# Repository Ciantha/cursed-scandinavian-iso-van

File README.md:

# cursed-scandinavian-iso-van
CC BY-NC 4.0

PCB work finished by the very kind josh-l-wang

## Images

## Disclaimer
The PCB design has been tested and confirmed to work. 
However, no one associated with this project (or anyone else) is liable if you end up with a non-functional pcb. 
Order at your own risk. Support will not be provided.

## Footprints and other tools

Uses footprints from https://github.com/ebastler/marbastlib
Thanks to zykrah for the very convenient KLE plugin https://github.com/zykrah/kicad-kle-placer#installation-kicad-7

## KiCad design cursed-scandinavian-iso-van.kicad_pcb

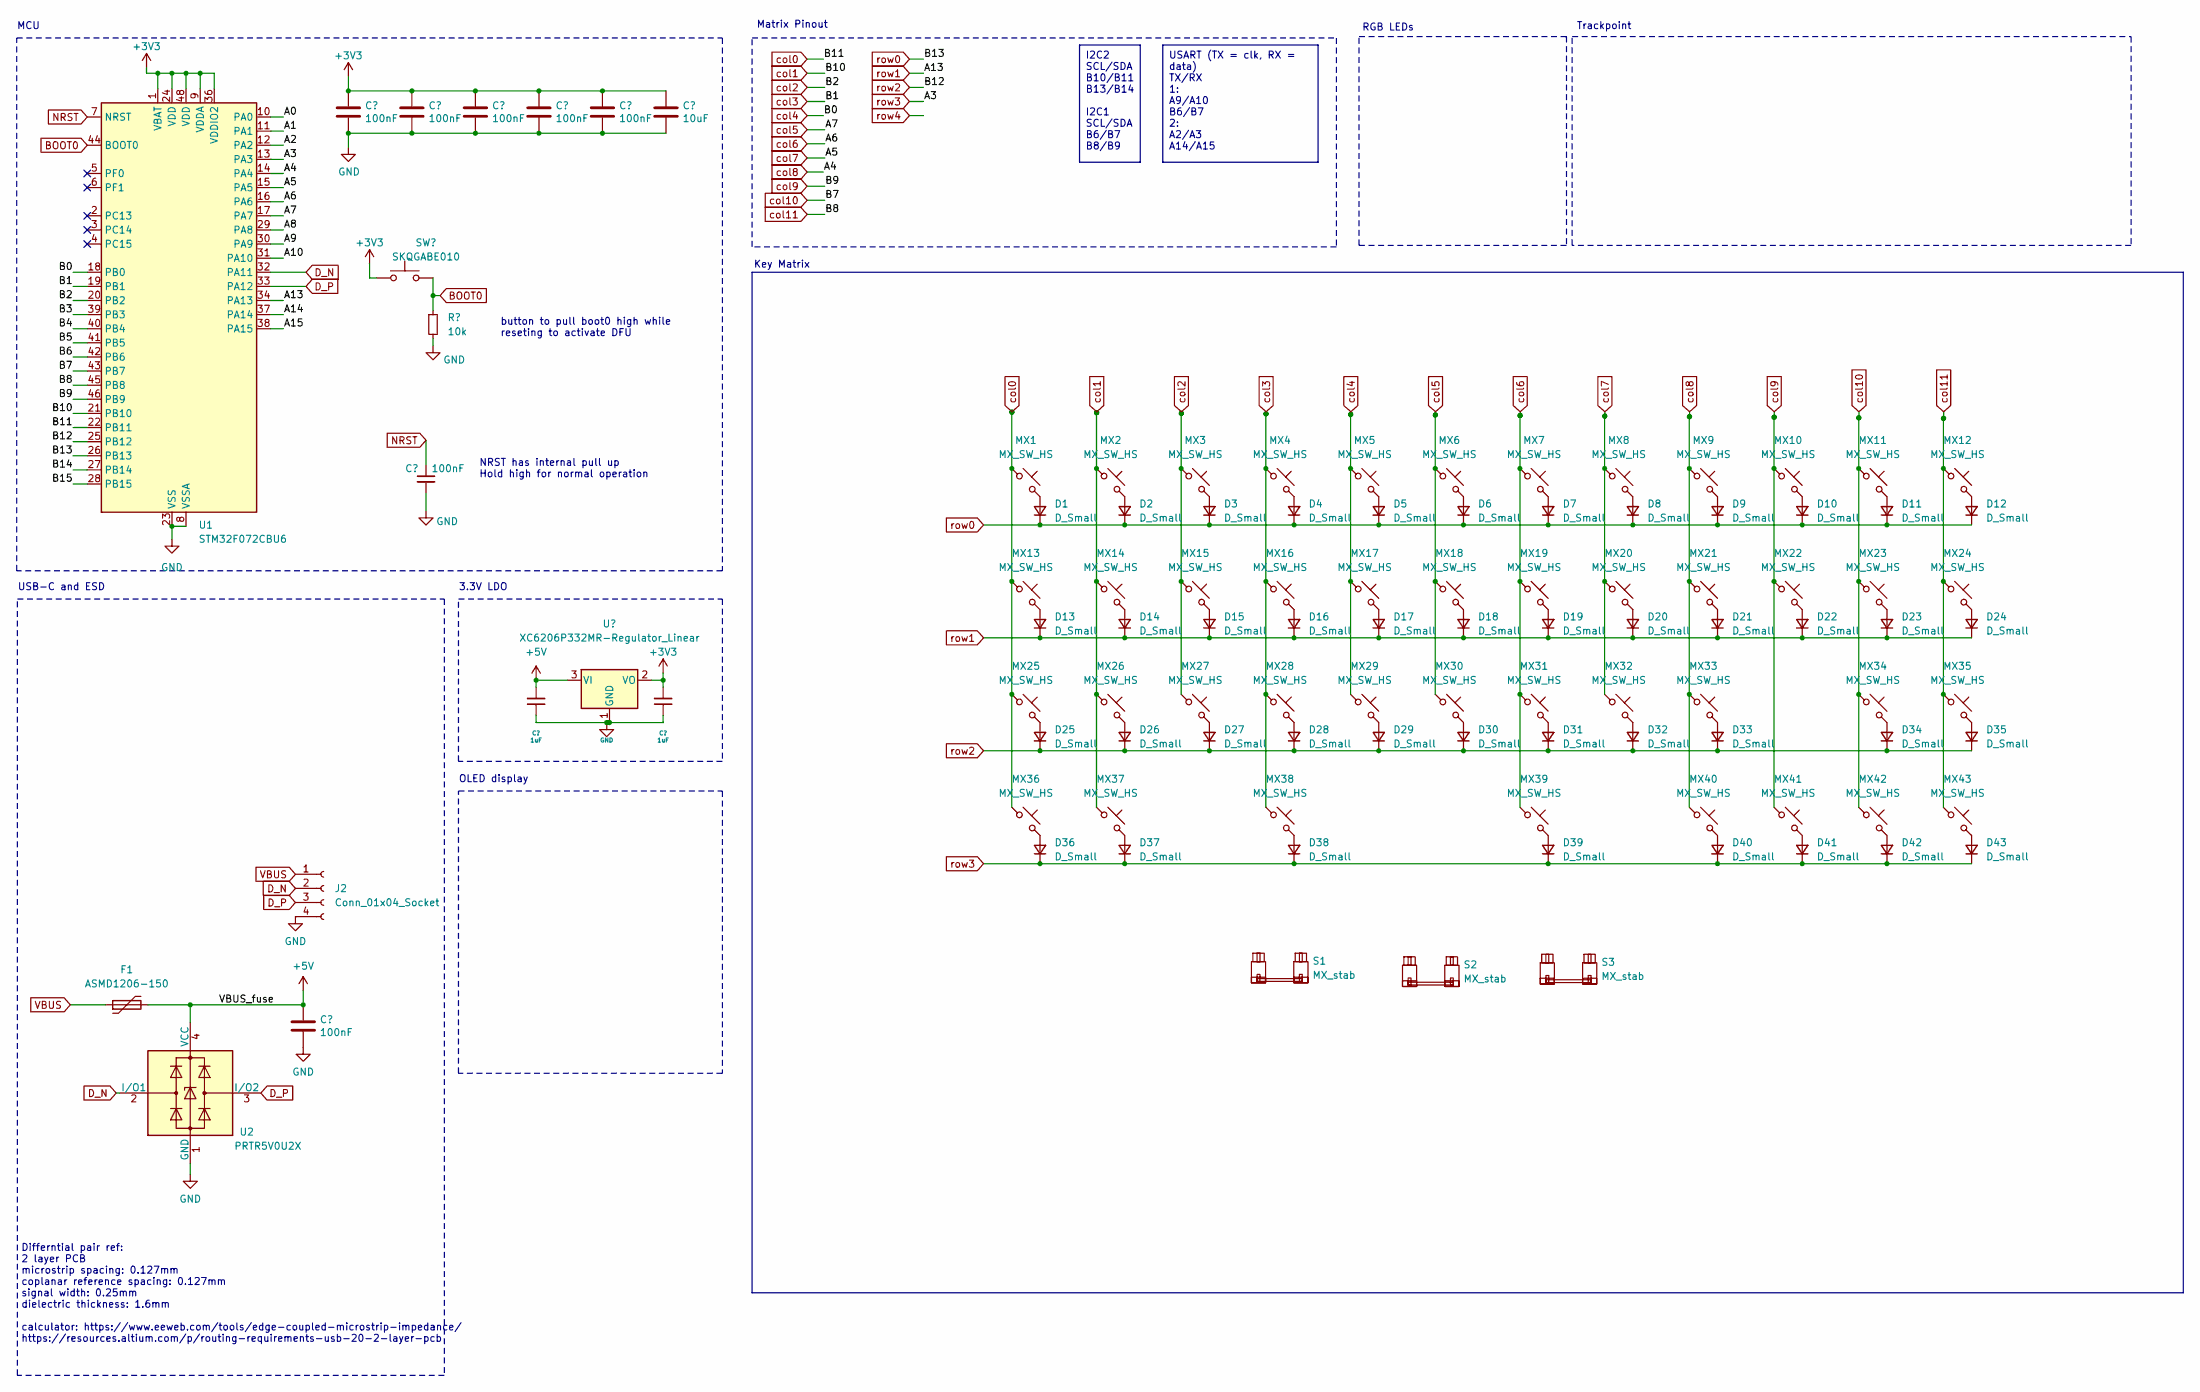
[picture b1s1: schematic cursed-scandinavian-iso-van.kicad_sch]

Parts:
C1, C2, C3, C4, C5, C7, C10: 100nF; C_0402_1005Metric; LCSC C307331
C6: 10uF; C_0603_1608Metric; LCSC C96446
C8, C9: 1uF; C_0402_1005Metric; LCSC C52923
D1, D2, D3, D4, D5, D6, D7, D8, D9, D10, D11, D12, D13, D14, D15, D16, D17, D18, D19, D20, D21, D22, D23, D24, D25, D26, D27, D28, D29, D30, D31, D32, D33, D34, D35, D36, D37, D38, D39, D40, D41, D42, D43: D_Small; D_SOD-123
F1: ASMD1206-150; Fuse_1206_3216Metric; LCSC C135341
J2: Conn_01x04_Socket; JST_SH_SM04B-SRSS-TB_1x04-1MP_P1.00mm_Horizontal
MX1, MX2, MX3, MX4, MX5, MX6, MX7, MX8, MX9, MX11, MX12, MX14, MX15, MX16, MX17, MX18, MX19, MX20, MX21, MX22, MX23, MX24, MX26, MX27, MX28, MX29, MX30, MX31, MX32, MX33, MX34, MX35, MX36, MX38, MX39, MX41, MX42, MX43: MX_SW_HS; SW_MX_HS_1u
MX10: MX_SW_HS; SW_MX_HS_1.75u
MX13, MX37, MX40: MX_SW_HS; SW_MX_HS_1.25u
MX25: MX_SW_HS; SW_MX_HS_1.5u
R1: 10k; R_0402_1005Metric; LCSC C25905
S1: MX_stab; STAB_MX_P_3u
S2: MX_stab; STAB_MX_P_2.75u
S3: MX_stab; STAB_MX_P_ISO-ROT
SW1: SKQGABE010; SW_SPST_SKQG_WithoutStem; LCSC C318884
U1: STM32F072CBU6; LQFP-48-1EP_7x7mm_P0.5mm_EP3.6x3.6mm; JlcRotOffset 90
U2: PRTR5V0U2X; SOT-143; LCSC C2827688
U3: XC6206P332MR-Regulator_Linear; SOT-23; LCSC C5446

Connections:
+3V3: C1.1, C2.1, C3.1, C4.1, C5.1, C6.1, C9.2, SW1.1, U1.1 (VBAT), U1.9 (VDDA), U1.24 (VDD), U1.36 (VDDIO2), U1.48 (VDD), U3.2 (VO)
+5V: C8.2, C10.1, F1.2, U2.4 (VCC), U3.3 (VI)
/A0: U1.10 (PA0)
/A1: U1.11 (PA1)
/A2: U1.12 (PA2)
/A8: U1.29 (PA8)
/A9: U1.30 (PA9)
/A10: U1.31 (PA10)
/A14: U1.37 (PA14)
/A15: U1.38 (PA15)
/B3: U1.39 (PB3)
/B4: U1.40 (PB4)
/B5: U1.41 (PB5)
/B6: U1.42 (PB6)
/B14: U1.27 (PB14)
/B15: U1.28 (PB15)
BOOT0: R1.1, SW1.2, U1.44 (BOOT0)
D_N: J2.2, U1.32 (PA11), U2.2 (I/O1)
D_P: J2.3, U1.33 (PA12), U2.3 (I/O2)
GND: C1.2, C2.2, C3.2, C4.2, C5.2, C6.2, C7.2, C8.1, C9.1, C10.2, J2.4, R1.2, U1.8 (VSSA), U1.23 (VSS), U1.35 (VSS), U1.47 (VSS), U1.49 (VSS), U2.1 (GND), U3.1 (GND)
NRST: C7.1, U1.7 (NRST)
unnamed: D1.2 (A), MX1.2
unnamed: D2.2 (A), MX2.2
unnamed: D3.2 (A), MX3.2
unnamed: D4.2 (A), MX4.2
unnamed: D5.2 (A), MX5.2
unnamed: D6.2 (A), MX6.2
unnamed: D7.2 (A), MX7.2
unnamed: D8.2 (A), MX8.2
unnamed: D9.2 (A), MX9.2
unnamed: D10.2 (A), MX10.2
unnamed: D11.2 (A), MX11.2
unnamed: D12.2 (A), MX12.2
unnamed: D13.2 (A), MX13.2
unnamed: D14.2 (A), MX14.2
unnamed: D15.2 (A), MX15.2
unnamed: D16.2 (A), MX16.2
unnamed: D17.2 (A), MX17.2
unnamed: D18.2 (A), MX18.2
unnamed: D19.2 (A), MX19.2
unnamed: D20.2 (A), MX20.2
unnamed: D21.2 (A), MX21.2
unnamed: D22.2 (A), MX22.2
unnamed: D23.2 (A), MX23.2
unnamed: D24.2 (A), MX24.2
unnamed: D25.2 (A), MX25.2
unnamed: D26.2 (A), MX26.2
unnamed: D27.2 (A), MX27.2
unnamed: D28.2 (A), MX28.2
unnamed: D29.2 (A), MX29.2
unnamed: D30.2 (A), MX30.2
unnamed: D31.2 (A), MX31.2
unnamed: D32.2 (A), MX32.2
unnamed 53: D33.2 (A), MX33.2; also elsewhere on the board
unnamed: D34.2 (A), MX34.2
unnamed: D35.2 (A), MX35.2
unnamed: D36.2 (A), MX36.2
unnamed: D37.2 (A), MX37.2
unnamed: D38.2 (A), MX38.2
unnamed: D39.2 (A), MX39.2
unnamed: D40.2 (A), MX40.2
unnamed: D41.2 (A), MX41.2
unnamed: D42.2 (A), MX42.2
unnamed: D43.2 (A), MX43.2
VBUS: F1.1, J2.1
col0: MX1.1, MX13.1, MX25.1, MX36.1, U1.22 (PB11)
col1: MX2.1, MX14.1, MX26.1, MX37.1, U1.21 (PB10)
col2: MX3.1, MX15.1, MX27.1, U1.20 (PB2)
col3: MX4.1, MX16.1, MX28.1, MX38.1, U1.19 (PB1)
col4: MX5.1, MX17.1, MX29.1, U1.18 (PB0)
col5: MX6.1, MX18.1, MX30.1, U1.17 (PA7)
col6: MX7.1, MX19.1, MX31.1, MX39.1, U1.16 (PA6)
col7: MX8.1, MX20.1, MX32.1, U1.15 (PA5)
col8: MX9.1, MX21.1, MX33.1, MX40.1, U1.14 (PA4); also elsewhere on the board
col9: MX10.1, MX22.1, MX41.1, U1.46 (PB9)
col10: MX11.1, MX23.1, MX34.1, MX42.1, U1.43 (PB7)
col11: MX12.1, MX24.1, MX35.1, MX43.1, U1.45 (PB8)
row0: D1.1 (K), D2.1 (K), D3.1 (K), D4.1 (K), D5.1 (K), D6.1 (K), D7.1 (K), D8.1 (K), D9.1 (K), D10.1 (K), D11.1 (K), D12.1 (K), U1.26 (PB13)
row1: D13.1 (K), D14.1 (K), D15.1 (K), D16.1 (K), D17.1 (K), D18.1 (K), D19.1 (K), D20.1 (K), D21.1 (K), D22.1 (K), D23.1 (K), D24.1 (K), U1.34 (PA13)
row2: D25.1 (K), D26.1 (K), D27.1 (K), D28.1 (K), D29.1 (K), D30.1 (K), D31.1 (K), D32.1 (K), D33.1 (K), D34.1 (K), D35.1 (K), U1.25 (PB12)
row3: D36.1 (K), D37.1 (K), D38.1 (K), D39.1 (K), D40.1 (K), D41.1 (K), D42.1 (K), D43.1 (K), U1.13 (PA3)

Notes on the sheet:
USART (TX = clk, RX = data) TX/RX 1: A9/A10 B6/B7 2: A2/A3 A14/A15
I2C2 SCL/SDA B10/B11 B13/B14 I2C1 SCL/SDA B6/B7 B8/B9
button to pull boot0 high while reseting to activate DFU
Matrix Pinout
MCU
RGB LEDs
Trackpoint
3.3V LDO
USB-C and ESD
OLED display
NRST has internal pull up Hold high for normal operation
Differntial pair ref: 2 layer PCB microstrip spacing: 0.127mm coplanar reference spacing: 0.127mm signal width: 0.25mm dielectric thickness: 1.6mm calculator: https://www.eeweb.com/tools/edge-coupled-microstrip-impedance/ https://resources.altium.com/p/routing-requirements-usb-20-2-layer-pcb
Key Matrix

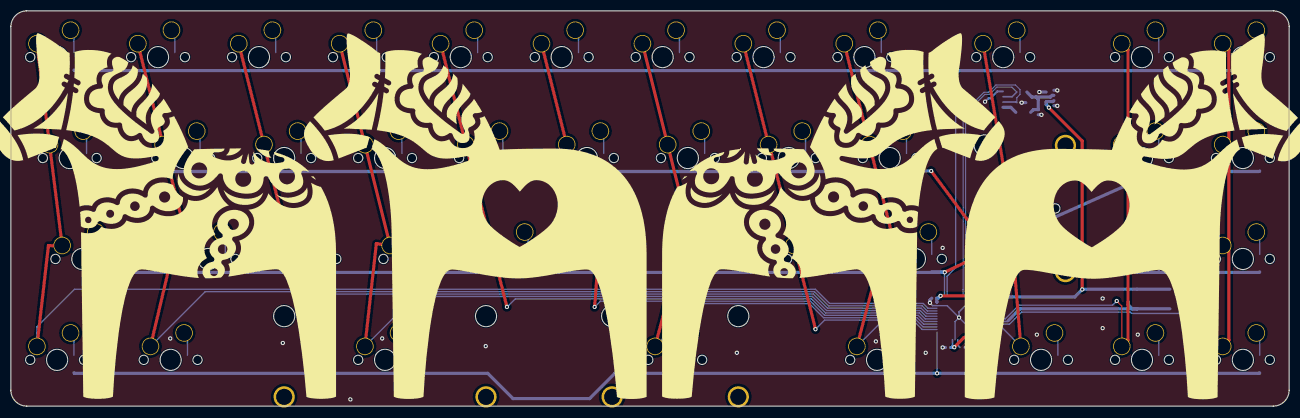
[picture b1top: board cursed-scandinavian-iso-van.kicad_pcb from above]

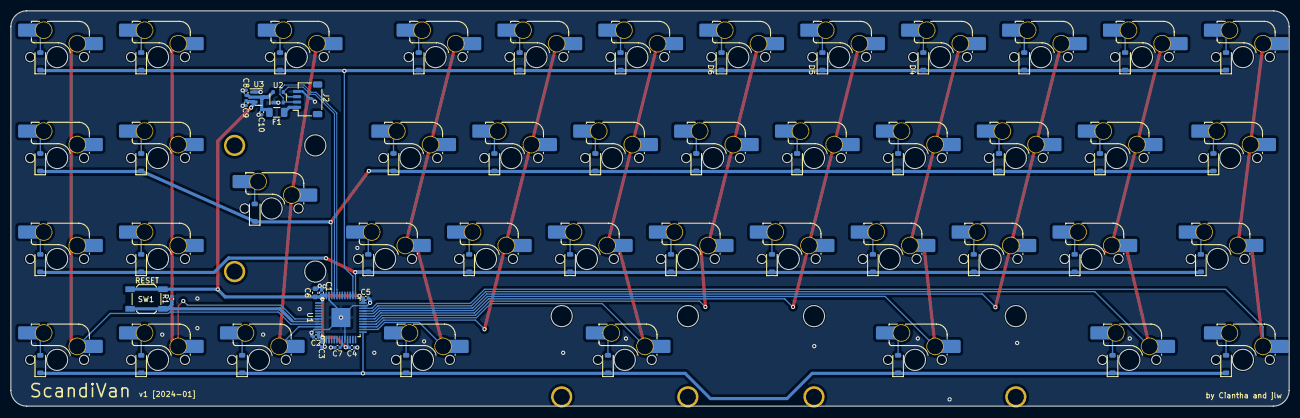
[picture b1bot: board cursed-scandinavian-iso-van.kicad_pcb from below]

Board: 2 copper layers, 241.3 x 74.6 mm, 106 parts (103 on the bottom side), 67 nets.

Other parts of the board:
locked: MX_SW_HS; SW_MX_HS_1u

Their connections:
unnamed 53: locked.2; also elsewhere on the board
col8: locked.1; also elsewhere on the board

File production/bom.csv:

Designator,Footprint,Quantity,Value,LCSC Part #
"C1, C10, C2, C3, C4, C5, C7",0402,7,100nF,C307331
C6,0603,1,10uF,C96446
"C8, C9",0402,2,1uF,C52923
"D1, D10, D11, D12, D13, D14, D15, D16, D17, D18, D19, D2, D20, D21, D22, D23, D24, D25, D26, D27, D28, D29, D3, D30, D31, D32, D33, D34, D35, D36, D37, D38, D39, D4, D40, D41, D42, D43, D5, D6, D7, D8, D9",D_SOD-123,43,D_Small,C81598
F1,1206,1,ASMD1206-150,C135341
J2,JST_SH_SM04B-SRSS-TB_1x04-1MP_P1.00mm_Horizontal,1,Conn_01x04_Socket,C160404
"MX1, MX11, MX12, MX14, MX15, MX16, MX17, MX18, MX19, MX2, MX20, MX21, MX22, MX23, MX24, MX26, MX27, MX28, MX29, MX3, MX30, MX31, MX32, MX33, MX34, MX35, MX36, MX38, MX39, MX4, MX41, MX42, MX43, MX5, MX6, MX7, MX8, MX9",SW_MX_HS_1u,38,MX_SW_HS,C5184526
MX10,SW_MX_HS_1.75u,1,MX_SW_HS,C5184526
"MX13, MX37, MX40",SW_MX_HS_1.25u,3,MX_SW_HS,C5184526
MX25,SW_MX_HS_1.5u,1,MX_SW_HS,C5184526
R1,0402,1,10k,C25905
SW1,SW_SPST_SKQG_WithoutStem,1,SKQGABE010,C318884
U1,LQFP-48-1EP_7x7mm_P0.5mm_EP3.6x3.6mm,1,STM32F072CBU6,C81720
U2,SOT-143,1,PRTR5V0U2X,C2827688
U3,SOT-23,1,XC6206P332MR-Regulator_Linear,C5446

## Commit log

2023-07-08 created kicad project
2023-07-08 first pass of schematic
2023-07-08 begun routing
2023-07-08 rerouted everything again
2023-07-08 maybe all the columns
2023-07-08 only silk and edge complaints
2023-07-09 hid silkscreen for diodes
2023-07-09 generated gerbers
2023-07-09 and one more save
2023-07-13 second attempt
2023-07-21 tuned data line
2023-07-21 maybe
2024-01-11 finish PCB in STM32
2024-01-11 add plates
    fit original MB44 cases
2024-01-12 updated PCB
2024-01-26 add VIAL firmware
2024-01-26 add pictures
2024-01-26 Update README.md with images
